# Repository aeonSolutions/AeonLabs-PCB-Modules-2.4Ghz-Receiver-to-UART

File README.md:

# AeonLabs PCB Modules:  2.4Ghz Receiver to UART
This is a pcb design module for a 2.4Ghz receiver to UART focused on all those Handheld Barcode & QR code scanners sold on AliExpress (see [here](https://s.click.aliexpress.com/e/_DFo4U4B)). Suitable as a add-on design for any other KiCad project.

*Don't forget to LIKE , SHARE and subscribe the free whatsApp group* and if you liked this PCB consider buying me a cup of coffee. Links below.

### Status
  Waiting for first batch from factory. Not tested.

If you already tested this PCB send me a message. Thank you

## Revisions
- revision 1.0
 
## Download options
Download this repository if you need the KiCad Files or, download the Gerber files in the release section of this repository

## Liked it ? Get a Free PCB for yourself
Send me your Device or hardware and i will design a custom PCB for it. Free of charge. Contact-me on WhatsApp or email for more info. 

## Q&A WhatsApp Group
If you have any Questions or simply  like this kind of projects and want to stay updated with the latest research ideas and prototypes during the day and week, join the WhatsApp Group
[A.I. Things](https://chat.whatsapp.com/FkNC7u83kuy2QRA5sqjBVg)

## Fully assembled PCB
Alternatively, and if you do not want to build a PCB by yourself and like to buy one, you can do it here:

The price will be around 30eur plus postage fees.
(I will also deliver the assembled PCB with all the components in place at a fair aditonal cost).

This PCB is a #direct fit #replacement of the one found on the internet at sale. For example here: https://s.click.aliexpress.com/e/_9wRPxz

#### Be supportive of my dedication and work towards technology education and buy me a coffee. Link below.

________________________________________________________________________________________________________________

## PCB Parts list
- [Capacitor 36pF SMD 0805](https://s.click.aliexpress.com/e/_AVdmzr)
- [Resistor SMD 1206 330R x3 ](https://s.click.aliexpress.com/e/_A7OXrR)
- [QFN20 XN297](https://s.click.aliexpress.com/e/_Dl894rH)
- [16Mhz Crystal](https://s.click.aliexpress.com/e/_DFmHH83)

## Firmware Download 
one can use the PCB in the repository [AeonLabs-MCU-Burner-USB-to-UART-TTL](https://github.com/aeonSolutions/AeonLabs-MCU-Burner-USB-to-UART-TTL) to program the ESP32 WROOM32 MCU on this PCB.

______________________________________________________________________________________________________________________________

### License
2022 Creative Commons Attribution-NonCommercial-ShareAlike 4.0 International

https://creativecommons.org/licenses/by-nc-sa/4.0/

### Own a copy of this work
if you like to own a copy of this work, you can buy it as a NFT or Ethereum. contact me for more details at mtpsilva@gmail.com
________________________________________________________________________________________________________________
## [Go back to main catalogue page](https://github.com/aeonSolutions/PCB-Prototyping-Catalogue)
________________________________________________________________________________________________________________

### Share this PCB board files

### Be supportive of my dedication and work towards technology education and buy me a coffee

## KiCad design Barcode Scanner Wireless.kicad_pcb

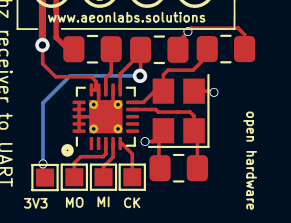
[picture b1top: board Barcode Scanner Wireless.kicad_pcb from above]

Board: 2 copper layers, 10 parts (0 on the bottom side), 8 nets.

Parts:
TP1, TP2, TP3: TestPoint; TestPoint_Pad_1.0x1.0mm
TP4: 3V3; TestPoint_Pad_1.0x1.0mm
U1: XN297_2.4Ghz_RF_UART; UQFN-20-1EP_3x3mm_P0.4mm_EP1.85x1.85mm_ThermalVias
XC1, XC2: 36pF; C_0805_2012Metric_Pad1.18x1.45mm_HandSolder
XC3: ????F; C_0805_2012Metric_Pad1.18x1.45mm_HandSolder
XC4: 100nF; C_0805_2012Metric_Pad1.18x1.45mm_HandSolder
XY1: 16Mhz; Crystal_SMD_3225-4Pin_3.2x2.5mm

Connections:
GND: U1.12 (ANTP), U1.14 (VSS2), U1.15 (VDD2), U1.16 (IREF), U1.17 (VSS3), U1.18 (VDDI), U1.19 (DVDD), U1.20 (VSS4), U1.21 (VSS), XC1.2, XC2.2, XC4.2, XY1.2, XY1.4
unnamed: TP1.1, U1.3 (SCLK)
unnamed: TP2.1, U1.4 (MISO)
unnamed: TP3.1, U1.5 (MOSI)
unnamed: U1.13 (ANTN), XC3.1
unnamed: U1.9 (XT1), XC1.1, XY1.1
unnamed: U1.10 (XT2), XC2.1, XY1.3
VDD_3V3: TP4.1, U1.11 (VDD_PA), XC4.1

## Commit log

2022-06-28 rev 1,0
